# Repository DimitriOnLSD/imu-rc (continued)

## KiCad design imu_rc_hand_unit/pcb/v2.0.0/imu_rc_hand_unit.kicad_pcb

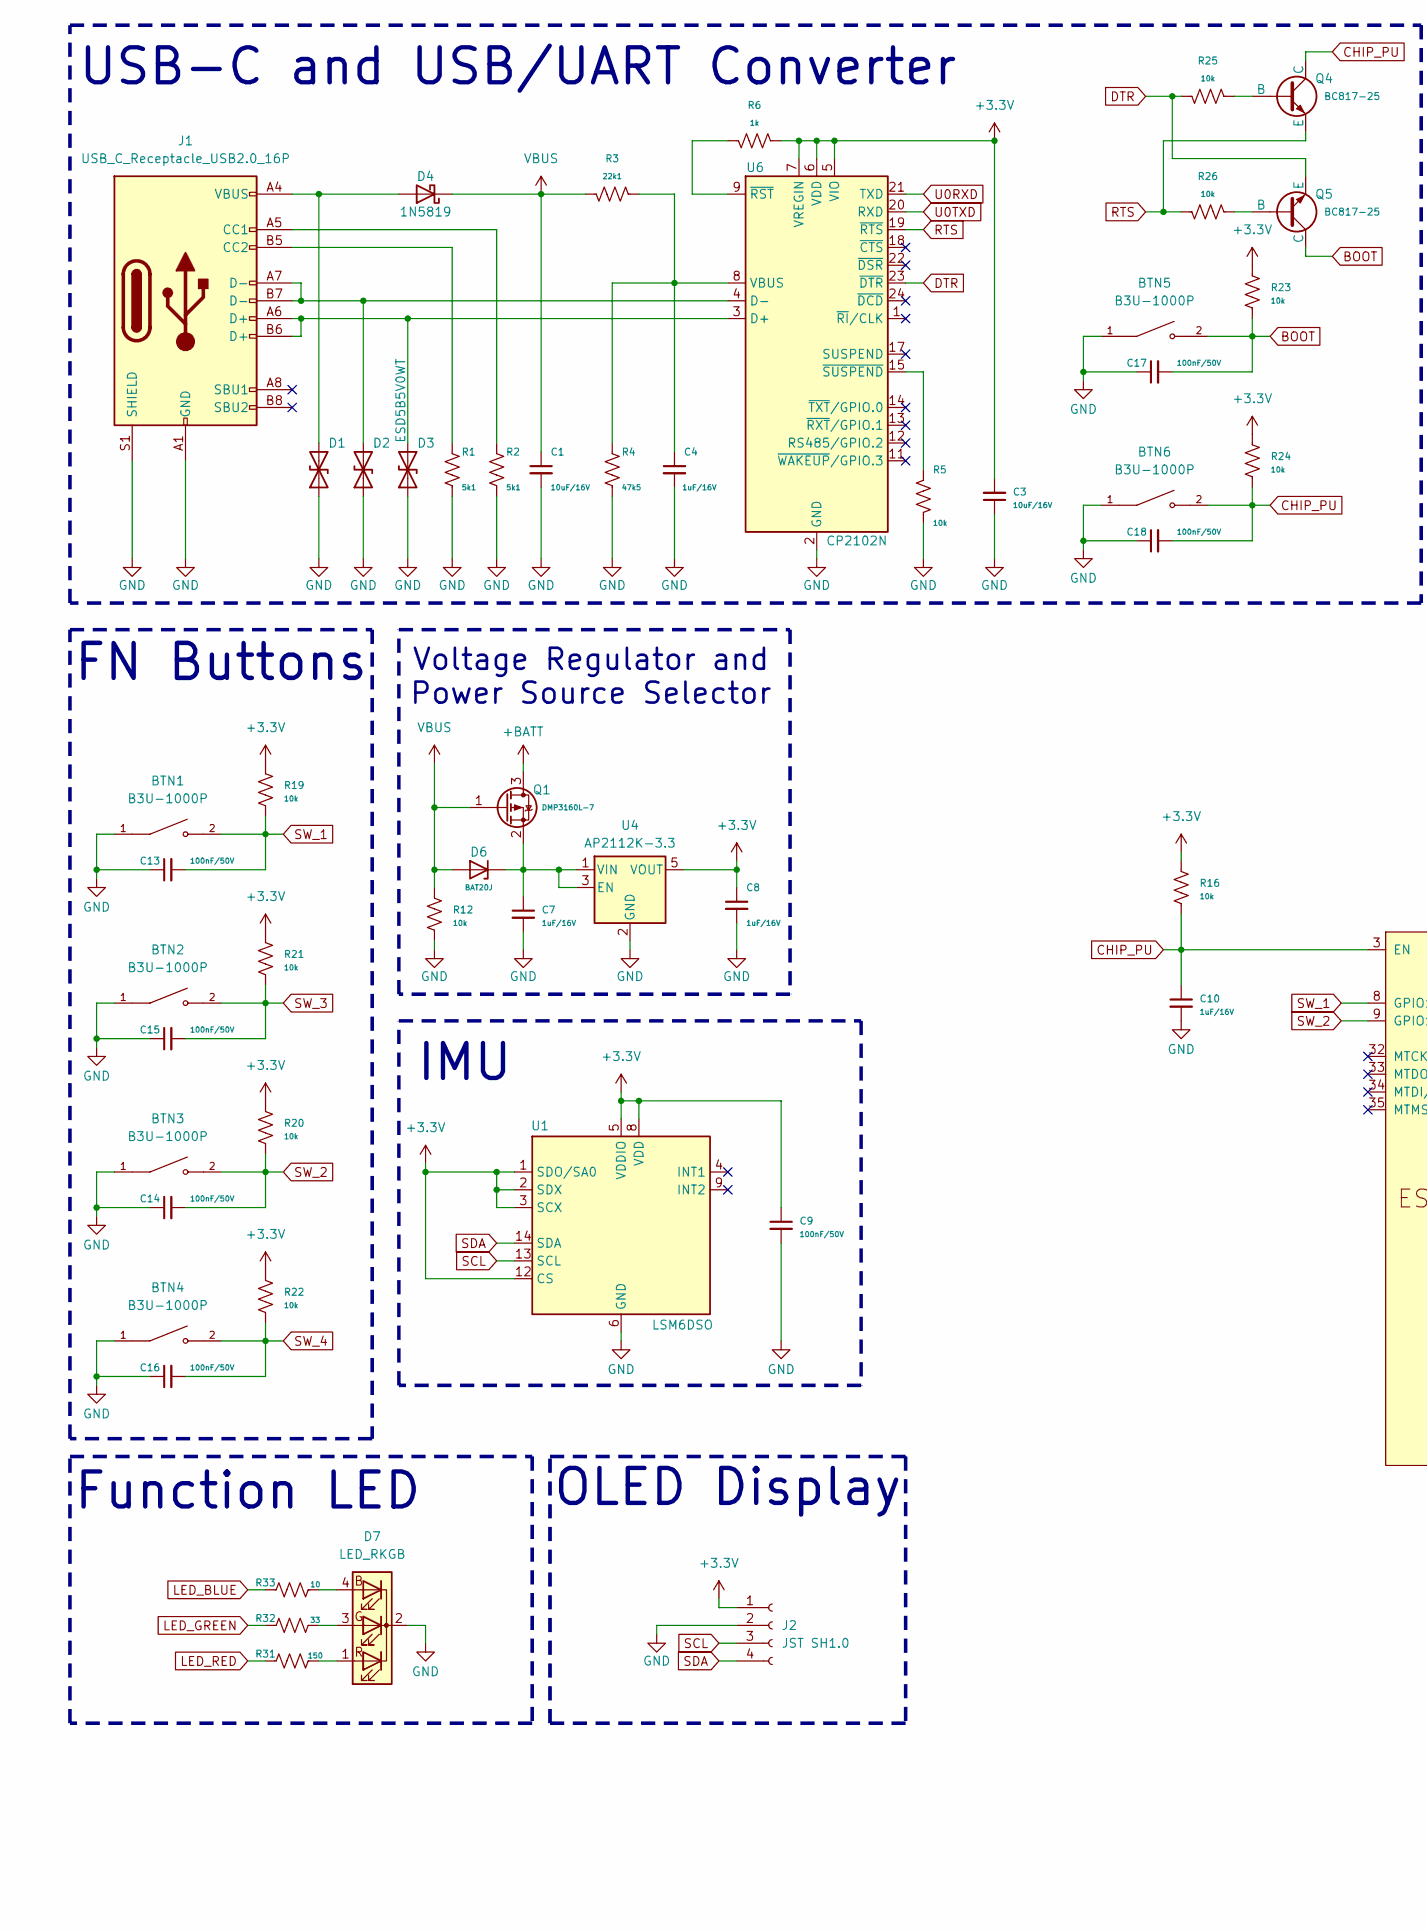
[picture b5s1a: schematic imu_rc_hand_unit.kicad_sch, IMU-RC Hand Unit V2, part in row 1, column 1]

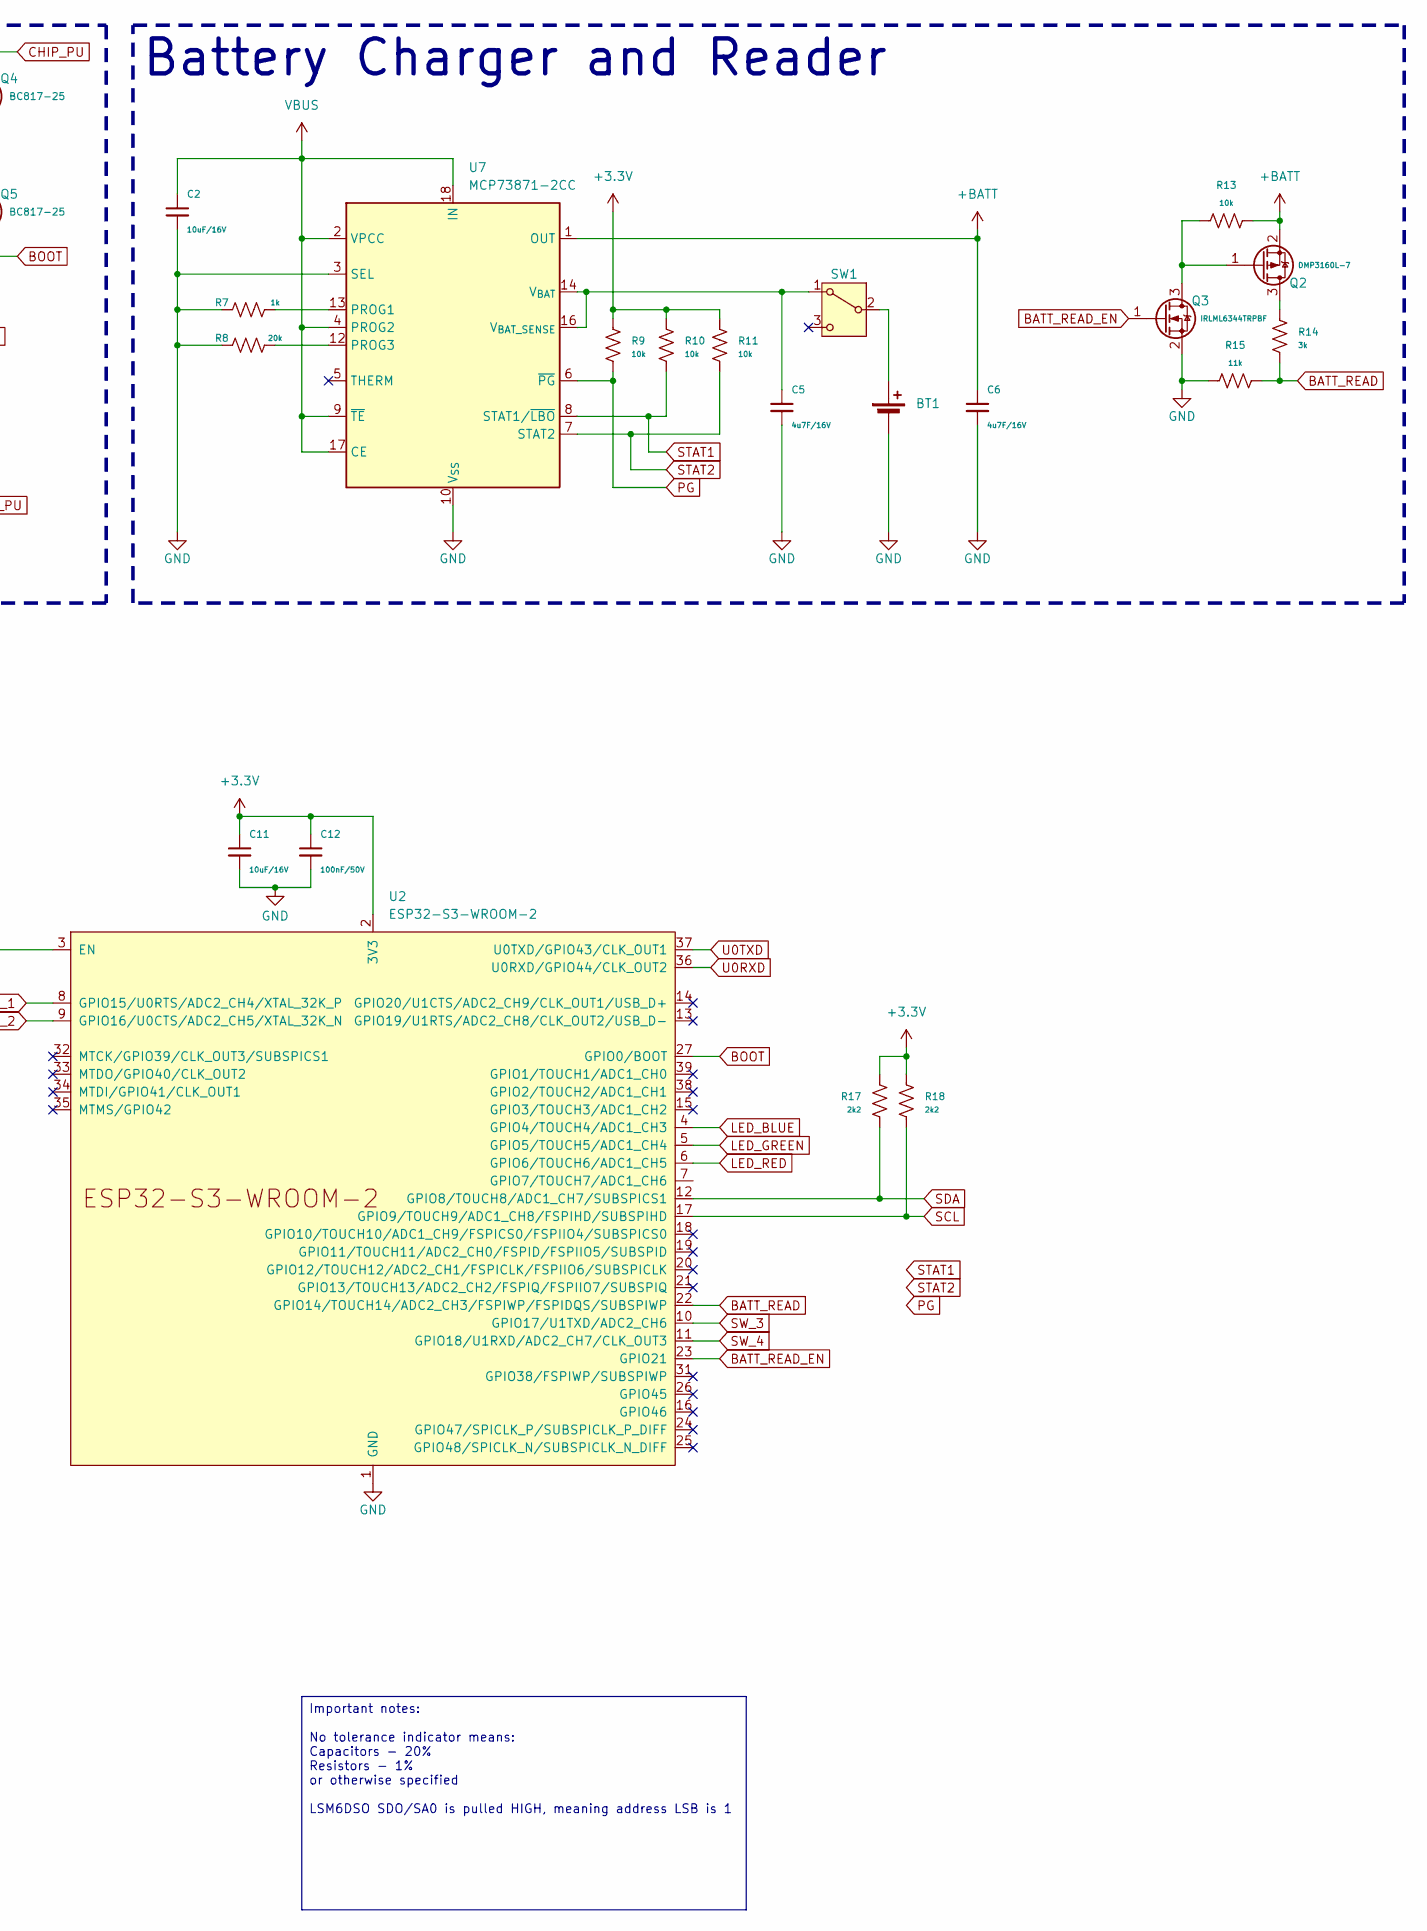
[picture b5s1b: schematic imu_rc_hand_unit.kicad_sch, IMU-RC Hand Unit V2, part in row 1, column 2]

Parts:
BT1: LiPo 3.7V 600mAh; JST_PH_S2B-PH-K_1x02_P2.00mm_Horizontal
BTN1, BTN2, BTN3, BTN4: B3U-1000P; SW_SPST_PTS647_Sx50
BTN5, BTN6: B3U-1000P; SW_SPST_B3U-1000P
C1, C2, C3, C11: 10uF/16V; C_0805_2012Metric
C4, C7, C8, C10: 1uF/16V; C_0805_2012Metric
C5, C6: 4u7F/16V; C_0805_2012Metric
C9, C12, C13, C14, C15, C16, C17, C18: 100nF/50V; C_0805_2012Metric
D1, D2, D3: ESD5B5V0WT; D_SOD-523
D4: 1N5819; D_SOD-123
D6: BAT20J; D_SOD-323
D7: LED_RKGB; LED_D5.0mm-4_RKGB
J1: USB_C_Receptacle_USB2.0_16P; USB_C_Receptacle_GCT_USB4105-xx-A_16P_TopMnt_Horizontal
J2: JST SH1.0; JST_SH_SM04B-SRSS-TB_1x04-1MP_P1.00mm_Horizontal
Q1, Q2: DMP3160L-7; SOT-23
Q3: IRLML6344TRPBF; SOT-23
Q4, Q5: BC817-25; SOT-23
R1, R2: 5k1; R_0805_2012Metric
R3: 22k1; R_0805_2012Metric
R4: 47k5; R_0805_2012Metric
R5, R9, R10, R11, R12, R13, R16, R19, R20, R21, R22, R23, R24, R25, R26: 10k; R_0805_2012Metric
R6, R7: 1k; R_0805_2012Metric
R8: 20k; R_0805_2012Metric
R14: 3k; R_0805_2012Metric
R15: 11k; R_0805_2012Metric
R17, R18: 2k2; R_0805_2012Metric
R31: 150; R_0805_2012Metric
R32: 33; R_0805_2012Metric
R33: 10; R_0805_2012Metric
SW1: SW_SPDT; SW_Slide_SPDT_Angled_CK_OS102011MA1Q
U1: LSM6DSO; LGA-14L_3x2.5mm_P0.5mm
U2: ESP32-S3-WROOM-2
U4: AP2112K-3.3; SOT-23-5
U6: CP2102N; QFN-24-1EP_4x4mm_P0.5mm_EP2.6x2.6mm
U7: MCP73871-2CC; QFN-20-1EP_4x4mm_P0.5mm_EP2.5x2.5mm

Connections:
+3.3V: C3.2, C8.1, C9.1, C11.1, C12.1, J2.1, R6.2, R9.1, R10.1, R11.1, R16.2, R17.1, R18.2, R19.2, R20.2, R21.2, R22.2, R23.2, R24.2, U1.1 (SDO/SA0), U1.2 (SDX), U1.3 (SCX), U1.5 (VDDIO), U1.8 (VDD), U1.12 (CS), U2.2 (3V3), U4.5 (VOUT), U6.5 (VIO), U6.6 (VDD), U6.7 (VREGIN)
+BATT: C6.1, Q1.3 (D), Q2.2 (S), R13.2, U7.1 (OUT), U7.20 (OUT)
BATT_READ: R14.2, R15.1, U2.22 (GPIO14/TOUCH14/ADC2_CH3/FSPIWP/FSPIDQS/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)
BATT_READ_EN: Q3.1 (G), U2.23 (GPIO21)
BOOT: BTN5.2, C17.2, Q5.1 (C), R23.1, U2.27 (GPIO0/BOOT)
CHIP_PU: BTN6.2, C10.1, C18.2, Q4.1 (C), R16.1, R24.1, U2.3 (EN)
DTR: Q5.3 (E), R25.1, U6.23 (~DTR)
GND: BT1.2 (-), BTN1.1, BTN2.1, BTN3.1, BTN4.1, BTN5.1, BTN6.1, C1.2, C2.2, C3.1, C4.2, C5.2, C6.2, C7.2, C8.2, C9.2, C10.2, C11.2, C12.2, C13.1, C14.1, C15.1, C16.1, C17.1, C18.1, D1.1 (A1), D2.1 (A1), D3.1 (A1), D7.2 (K), J1.A1 (GND), J1.A12 (GND), J1.B1 (GND), J1.B12 (GND), J1.S1 (SHIELD), J2.2, Q3.2 (S), R1.1, R2.1, R4.1, R5.2, R7.2, R8.2, R12.1, R15.2, U1.6 (GND), U1.7 (GND), U2.1 (GND), U2.40 (GND), U2.41 (GND), U4.2 (GND), U6.2 (GND), U6.25 (GND), U7.3 (SEL), U7.10 (V_{SS}), U7.11 (V_{SS}), U7.21 (V_{SS})
LED_BLUE: R33.2, U2.4 (GPIO4/TOUCH4/ADC1_CH3)
LED_GREEN: R32.2, U2.5 (GPIO5/TOUCH5/ADC1_CH4)
LED_RED: R31.2, U2.6 (GPIO6/TOUCH6/ADC1_CH5)
unnamed: BT1.1 (+), SW1.2 (B)
unnamed: D1.2 (A2), D4.2 (A), J1.A4 (VBUS), J1.A9 (VBUS), J1.B4 (VBUS), J1.B9 (VBUS)
unnamed: D2.2 (A2), J1.A7 (D-), J1.B7 (D-), U6.4 (D-)
unnamed: D3.2 (A2), J1.A6 (D+), J1.B6 (D+), U6.3 (D+)
unnamed: C7.1, D6.1 (K), Q1.2 (S), U4.1 (VIN), U4.3 (EN)
unnamed: D7.4 (BA), R33.1
unnamed: D7.3 (GA), R32.1
unnamed: D7.1 (RA), R31.1
unnamed: J1.A5 (CC1), R2.2
unnamed: J1.B5 (CC2), R1.2
unnamed: Q2.3 (D), R14.1
unnamed: Q2.1 (G), Q3.3 (D), R13.1
unnamed: Q4.2 (B), R25.2
unnamed: Q5.2 (B), R26.2
unnamed: C5.1, SW1.1 (A), U7.14 (V_{BAT}), U7.15 (V_{BAT}), U7.16 (V_{BAT_SENSE})
unnamed: C4.1, R3.1, R4.2, U6.8 (VBUS)
unnamed: R6.1, U6.9 (~RST)
unnamed: R5.1, U6.15 (~SUSPEND)
unnamed: R7.1, U7.13 (PROG1)
unnamed: R8.1, U7.12 (PROG3)
PG: R9.2, U7.6 (~PG)
RTS: Q4.3 (E), R26.1, U6.19 (~RTS)
SCL: J2.3, R18.1, U1.13 (SCL), U2.17 (GPIO9/TOUCH9/ADC1_CH8/FSPIHD/SUBSPIHD)
SDA: J2.4, R17.2, U1.14 (SDA), U2.12 (GPIO8/TOUCH8/ADC1_CH7/SUBSPICS1)
STAT1: R10.2, U7.8 (STAT1/~LBO)
STAT2: R11.2, U7.7 (STAT2)
SW_1: BTN1.2, C13.2, R19.1, U2.8 (GPIO15/U0RTS/ADC2_CH4/XTAL_32K_P)
SW_2: BTN3.2, C14.2, R20.1, U2.9 (GPIO16/U0CTS/ADC2_CH5/XTAL_32K_N)
SW_3: BTN2.2, C15.2, R21.1, U2.10 (GPIO17/U1TXD/ADC2_CH6)
SW_4: BTN4.2, C16.2, R22.1, U2.11 (GPIO18/U1RXD/ADC2_CH7/CLK_OUT3)
U0RXD: U2.36 (U0RXD/GPIO44/CLK_OUT2), U6.21 (TXD)
U0TXD: U2.37 (U0TXD/GPIO43/CLK_OUT1), U6.20 (RXD)
VBUS: C1.1, C2.1, D4.1 (K), D6.2 (A), Q1.1 (G), R3.2, R12.2, U7.2 (VPCC), U7.4 (PROG2), U7.9 (~TE), U7.17 (CE), U7.18 (IN), U7.19 (IN)

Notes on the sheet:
Voltage Regulator and Power Source Selector
Battery Charger and Reader
FN Buttons
USB-C and USB/UART Converter
IMU
OLED Display
Function LED
Important notes: No tolerance indicator means: Capacitors - 20% Resistors - 1% or otherwise specified LSM6DSO SDO/SA0 is pulled HIGH, meaning address LSB is 1

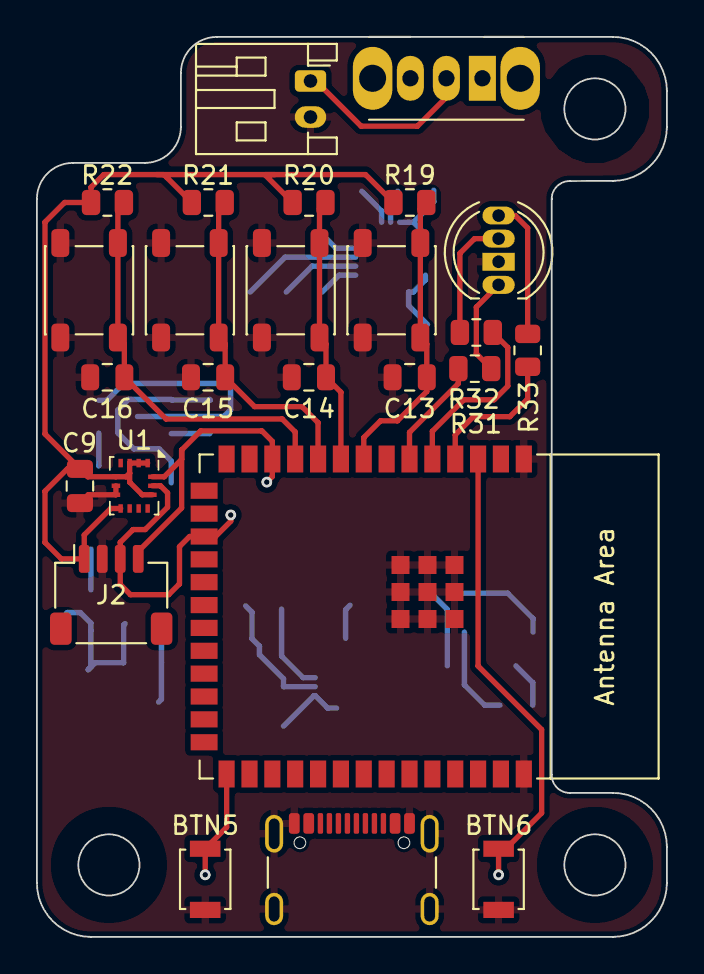
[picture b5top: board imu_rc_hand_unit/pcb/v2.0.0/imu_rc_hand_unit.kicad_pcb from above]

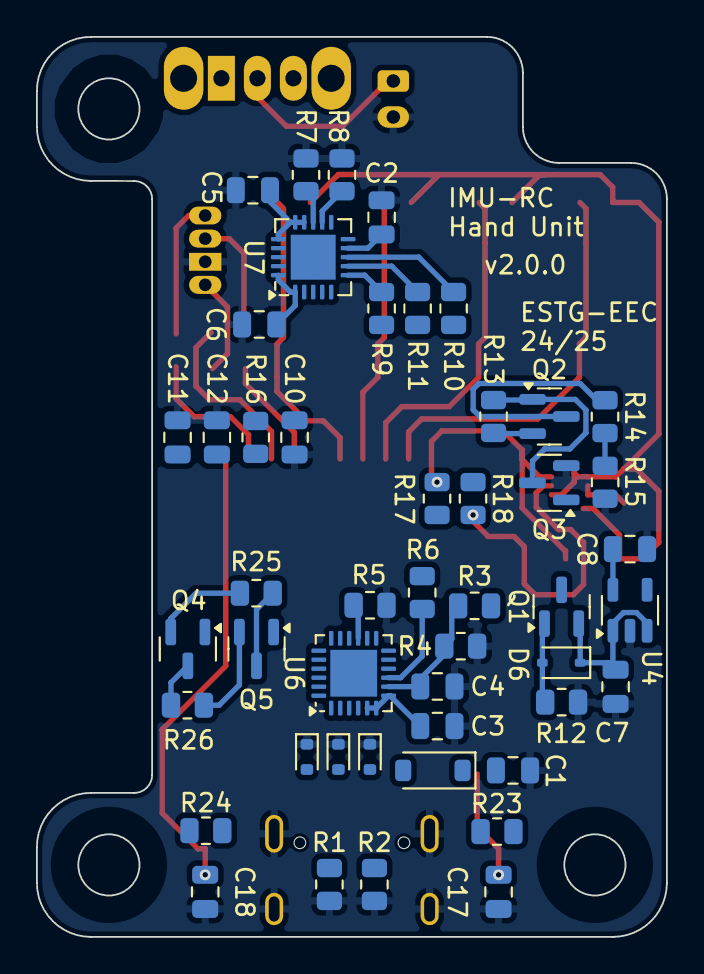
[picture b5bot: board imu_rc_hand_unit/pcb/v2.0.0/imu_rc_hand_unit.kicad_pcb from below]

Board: 2 copper layers, 35.0 x 50.0 mm, 73 parts (48 on the bottom side), 44 nets.

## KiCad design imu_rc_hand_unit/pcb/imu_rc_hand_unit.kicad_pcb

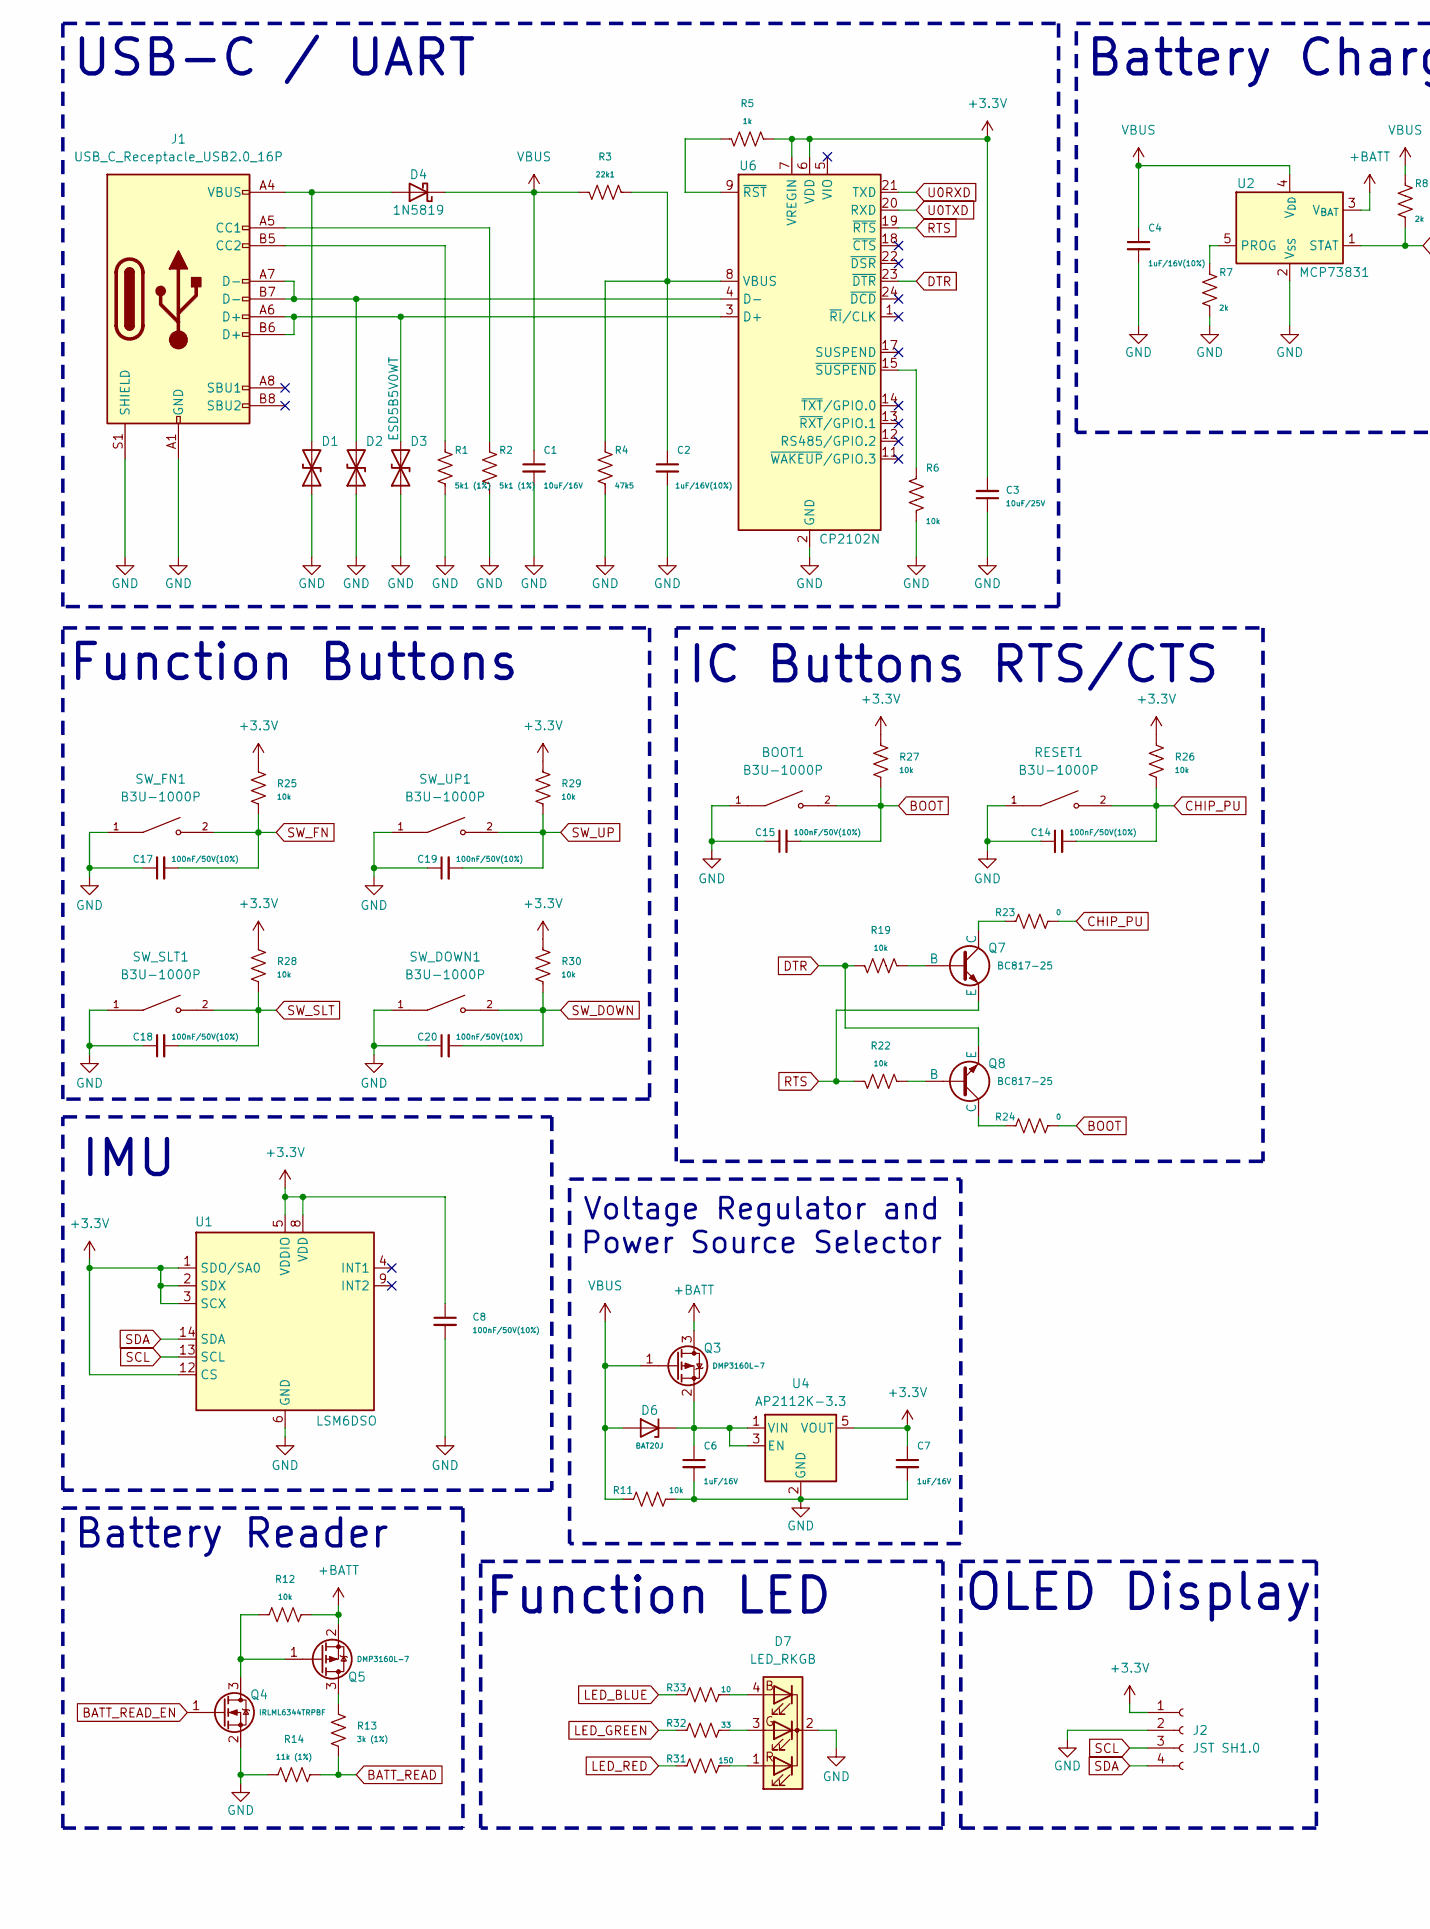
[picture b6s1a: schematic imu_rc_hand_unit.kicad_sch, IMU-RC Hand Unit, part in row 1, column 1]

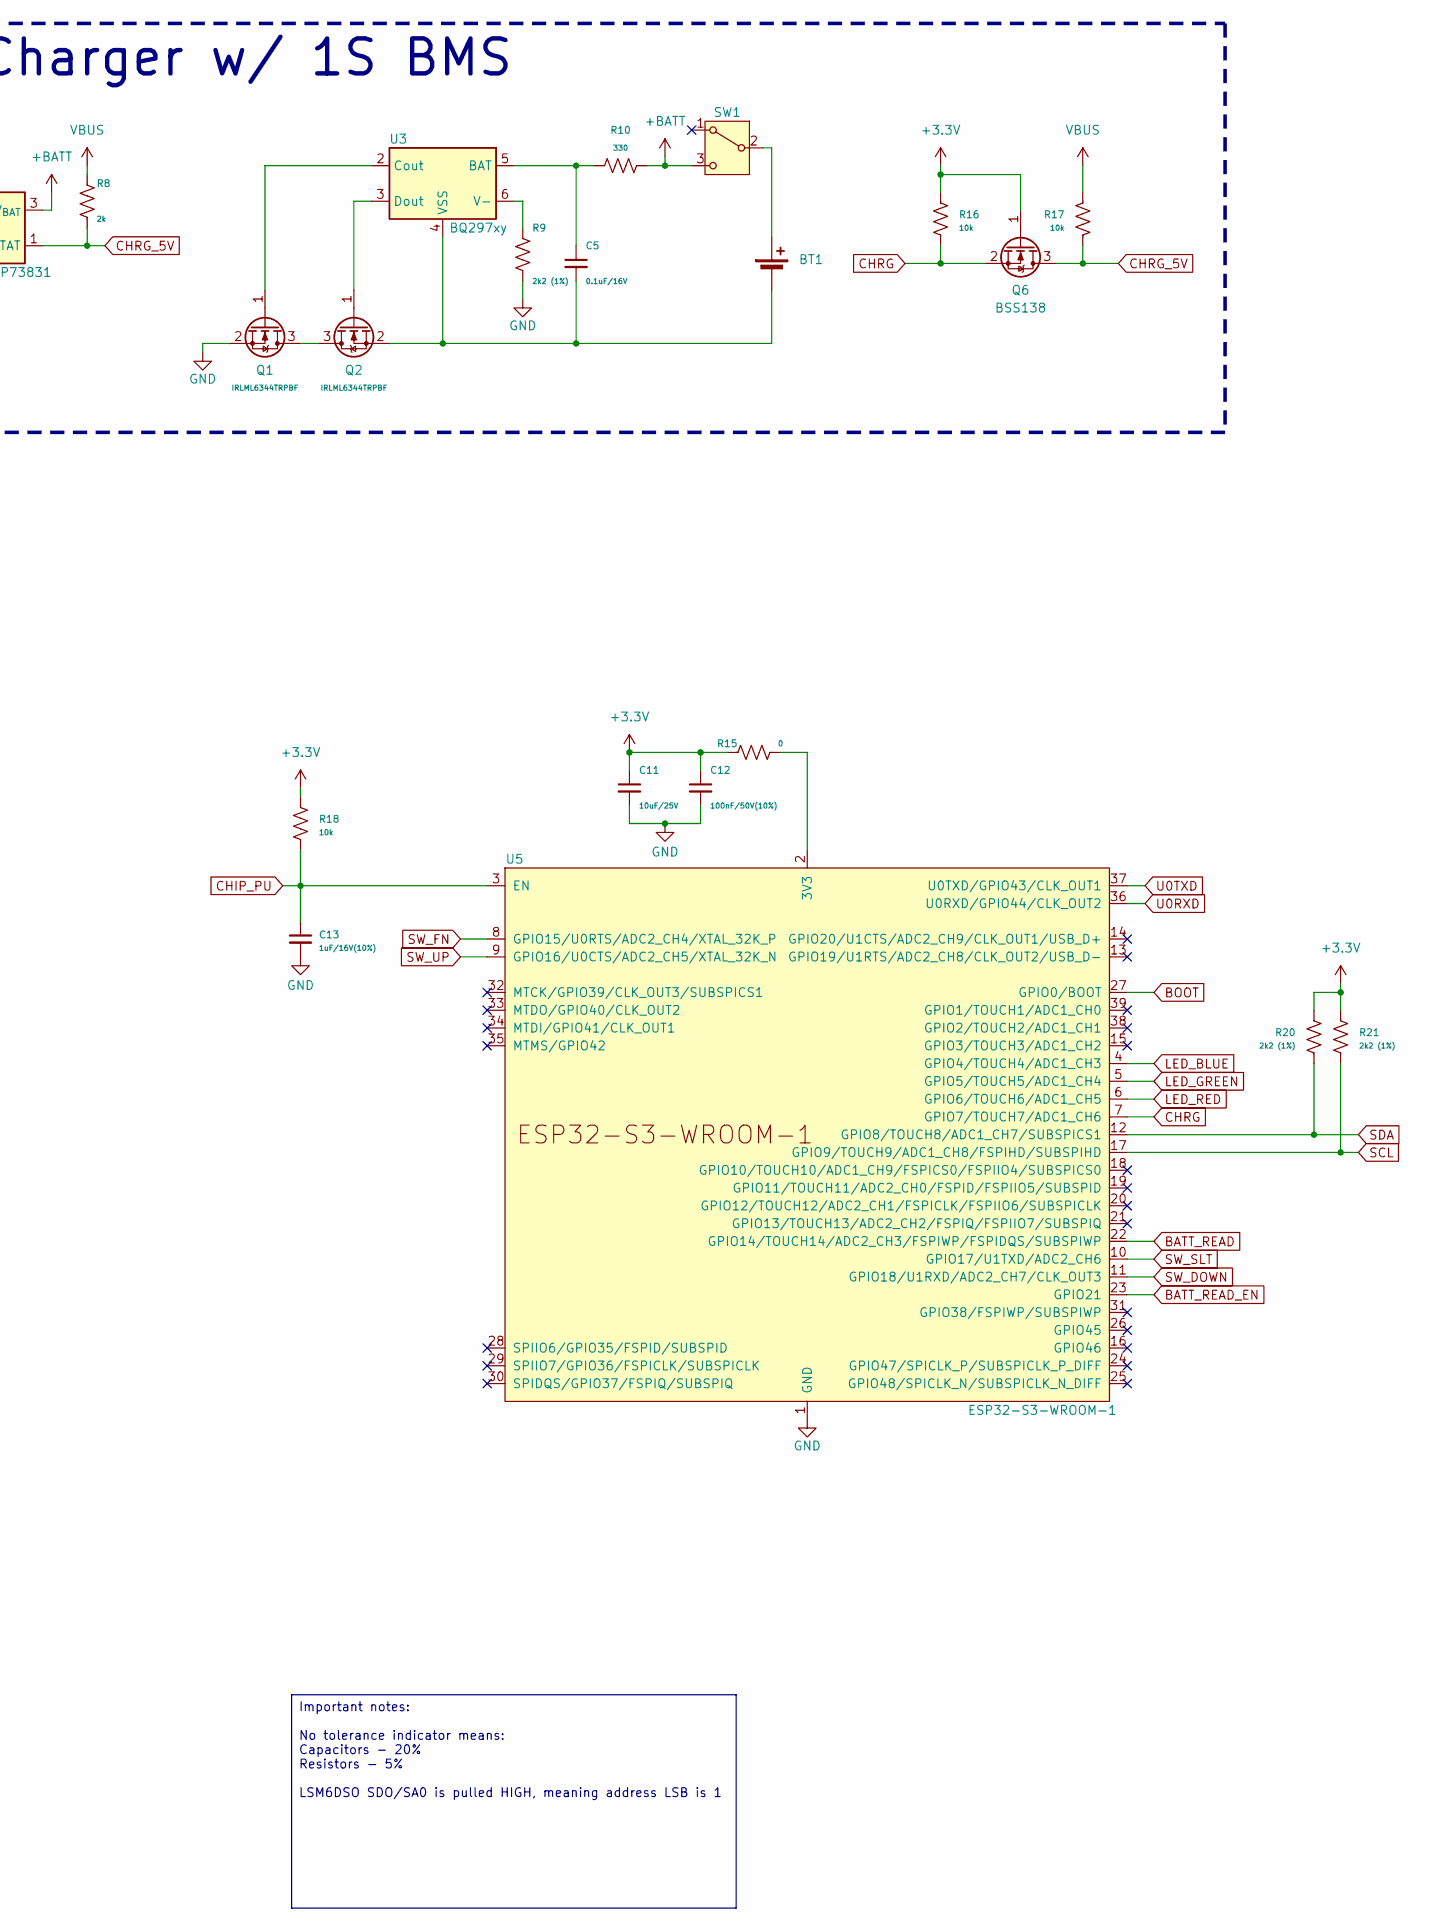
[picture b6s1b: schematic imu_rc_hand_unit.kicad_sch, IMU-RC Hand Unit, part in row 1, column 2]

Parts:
BOOT1: B3U-1000P; SW_SPST_B3U-1000P
BT1: LiPo 3.7V 600mAh; JST_PH_S2B-PH-K_1x02_P2.00mm_Horizontal
C1: 10uF/16V; C_0805_2012Metric
C2, C4: 1uF/16V(10%); C_0603_1608Metric
C3: 10uF/25V; C_0603_1608Metric
C5: 0.1uF/16V; C_0603_1608Metric
C6, C7: 1uF/16V; C_0805_2012Metric
C8, C12, C14, C15, C17, C18, C19, C20: 100nF/50V(10%); C_0805_2012Metric
C11: 10uF/25V; C_0805_2012Metric
C13: 1uF/16V(10%); C_0805_2012Metric
D1, D2: LESD5D5.0CT1G; D_SOD-523
D3: ESD5B5V0WT; D_SOD-523
D4: 1N5819; D_SOD-123
D6: BAT20J; D_SOD-323
D7: LED_RKGB; LED_D5.0mm-4_RKGB
J1: USB_C_Receptacle_USB2.0_16P; USB_C_Receptacle_GCT_USB4105-xx-A_16P_TopMnt_Horizontal
J2: JST SH1.0; JST_SH_SM04B-SRSS-TB_1x04-1MP_P1.00mm_Horizontal
Q1, Q2, Q4: IRLML6344TRPBF; SOT-23
Q3, Q5: DMP3160L-7; SOT-23
Q6: BSS138; SOT-23
Q7, Q8: BC817-25; SOT-23
R1, R2: 5k1 (1%); R_0805_2012Metric
R3: 22k1; R_0805_2012Metric
R4: 47k5; R_0805_2012Metric
R5: 1k; R_0805_2012Metric
R6, R11, R12, R16, R17, R18, R19, R22, R25, R26, R27, R28, R29, R30: 10k; R_0805_2012Metric
R7, R8: 2k; R_0805_2012Metric
R9, R20, R21: 2k2 (1%); R_0805_2012Metric
R10: 330; R_0805_2012Metric
R13: 3k (1%); R_0805_2012Metric
R14: 11k (1%); R_0805_2012Metric
R15, R23, R24: 0; R_1206_3216Metric
R31: 150; R_0805_2012Metric
R32: 33; R_0805_2012Metric
R33: 10; R_0805_2012Metric
RESET1: B3U-1000P; SW_SPST_B3U-1000P
SW1: SW_SPDT; SW_Slide_SPDT_Angled_CK_OS102011MA1Q
SW_DOWN1: B3U-1000P; SW_SPST_PTS647_Sx50
SW_FN1: B3U-1000P; SW_SPST_PTS647_Sx50
SW_SLT1: B3U-1000P; SW_SPST_PTS647_Sx50
SW_UP1: B3U-1000P; SW_SPST_PTS647_Sx50
U1: LSM6DSO; LGA-14L_3x2.5mm_P0.5mm
U2: MCP73831; QFN-20-1EP_4x4mm_P0.5mm_EP2.5x2.5mm
U3: BQ297xy; WSON-6_1.5x1.5mm_P0.5mm
U4: AP2112K-3.3; SOT-23-5
U5: ESP32-S3-WROOM-1
U6: CP2102N; QFN-24-1EP_4x4mm_P0.5mm_EP2.6x2.6mm

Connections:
+3.3V: C3.2, C7.1, C8.1, C11.1, C12.1, J2.1, Q6.1 (G), R5.2, R15.1, R16.2, R18.2, R20.1, R21.2, R25.2, R26.2, R27.2, R28.2, R29.2, R30.2, U1.1 (SDO/SA0), U1.2 (SDX), U1.3 (SCX), U1.5 (VDDIO), U1.8 (VDD), U1.12 (CS), U4.5 (VOUT), U6.6 (VDD), U6.7 (VREGIN)
+BATT: Q3.3 (D), Q5.2 (S), R10.2, R12.2, SW1.3 (C), U2.3 (V_{BAT})
BATT_READ: R13.2, R14.1, U5.22 (GPIO14/TOUCH14/ADC2_CH3/FSPIWP/FSPIDQS/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)
BATT_READ_EN: Q4.1 (G), U5.23 (GPIO21)
BOOT: BOOT1.2, C15.2, R24.2, R27.1, U5.27 (GPIO0/BOOT)
CHIP_PU: C13.1, C14.2, R18.1, R23.2, R26.1, RESET1.2, U5.3 (EN)
CHRG: Q6.2 (S), R16.1, U5.7 (GPIO7/TOUCH7/ADC1_CH6)
CHRG_5V: Q6.3 (D), R8.2, R17.1, U2.1 (STAT)
DTR: Q8.3 (E), R19.1, U6.23 (~DTR)
GND: BOOT1.1, C1.2, C2.2, C3.1, C4.2, C6.2, C7.2, C8.2, C11.2, C12.2, C13.2, C14.1, C15.1, C17.1, C18.1, C19.1, C20.1, D1.1 (A1), D2.1 (A1), D3.1 (A1), D7.2 (K), J1.A1 (GND), J1.A12 (GND), J1.B1 (GND), J1.B12 (GND), J1.S1 (SHIELD), J2.2, Q1.2 (S), Q4.2 (S), R1.1, R2.1, R4.1, R6.2, R7.2, R9.1, R11.1, R14.2, RESET1.1, SW_DOWN1.1, SW_FN1.1, SW_SLT1.1, SW_UP1.1, U1.6 (GND), U1.7 (GND), U2.2 (V_{SS}), U4.2 (GND), U5.1 (GND), U5.40 (GND), U5.41 (GND), U6.2 (GND), U6.25 (GND)
LED_BLUE: R33.2, U5.4 (GPIO4/TOUCH4/ADC1_CH3)
LED_GREEN: R32.2, U5.5 (GPIO5/TOUCH5/ADC1_CH4)
LED_RED: R31.2, U5.6 (GPIO6/TOUCH6/ADC1_CH5)
unnamed: BT1.1 (+), SW1.2 (B)
unnamed: BT1.2 (-), C5.2, Q2.2 (S), U3.4 (VSS)
unnamed: D1.2 (A2), D4.2 (A), J1.A4 (VBUS), J1.A9 (VBUS), J1.B4 (VBUS), J1.B9 (VBUS)
unnamed: D2.2 (A2), J1.A7 (D-), J1.B7 (D-), U6.4 (D-)
unnamed: D3.2 (A2), J1.A6 (D+), J1.B6 (D+), U6.3 (D+)
unnamed: C6.1, D6.1 (K), Q3.2 (S), U4.1 (VIN), U4.3 (EN)
unnamed: D7.4 (BA), R33.1
unnamed: D7.3 (GA), R32.1
unnamed: D7.1 (RA), R31.1
unnamed: J1.A5 (CC1), R2.2
unnamed: J1.B5 (CC2), R1.2
unnamed: Q1.3 (D), Q2.3 (D)
unnamed: Q1.1 (G), U3.2 (Cout)
unnamed: Q2.1 (G), U3.3 (Dout)
unnamed: Q4.3 (D), Q5.1 (G), R12.1
unnamed: Q5.3 (D), R13.1
unnamed: Q7.2 (B), R19.2
unnamed: Q7.1 (C), R23.1
unnamed: Q8.2 (B), R22.2
unnamed: Q8.1 (C), R24.1
unnamed: R7.1, U2.5 (PROG)
unnamed: C5.1, R10.1, U3.5 (BAT)
unnamed: R9.2, U3.6 (V-)
unnamed: R15.2, U5.2 (3V3)
unnamed: C2.1, R3.1, R4.2, U6.8 (VBUS)
unnamed: R5.1, U6.9 (~RST)
unnamed: R6.1, U6.15 (~SUSPEND)
RTS: Q7.3 (E), R22.1, U6.19 (~RTS)
SCL: J2.3, R21.1, U1.13 (SCL), U5.17 (GPIO9/TOUCH9/ADC1_CH8/FSPIHD/SUBSPIHD)
SDA: J2.4, R20.2, U1.14 (SDA), U5.12 (GPIO8/TOUCH8/ADC1_CH7/SUBSPICS1)
SW_DOWN: C20.2, R30.1, SW_DOWN1.2, U5.11 (GPIO18/U1RXD/ADC2_CH7/CLK_OUT3)
SW_FN: C17.2, R25.1, SW_FN1.2, U5.8 (GPIO15/U0RTS/ADC2_CH4/XTAL_32K_P)
SW_SLT: C18.2, R28.1, SW_SLT1.2, U5.10 (GPIO17/U1TXD/ADC2_CH6)
SW_UP: C19.2, R29.1, SW_UP1.2, U5.9 (GPIO16/U0CTS/ADC2_CH5/XTAL_32K_N)
U0RXD: U5.36 (U0RXD/GPIO44/CLK_OUT2), U6.21 (TXD)
U0TXD: U5.37 (U0TXD/GPIO43/CLK_OUT1), U6.20 (RXD)
VBUS: C1.1, C4.1, D4.1 (K), D6.2 (A), Q3.1 (G), R3.2, R8.1, R11.2, R17.2, U2.4 (V_{DD})

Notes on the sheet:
Voltage Regulator and Power Source Selector
Battery Charger w/ 1S BMS
Function Buttons
IC Buttons RTS/CTS
USB-C / UART
Battery Reader
IMU
OLED Display
Function LED
Important notes: No tolerance indicator means: Capacitors - 20% Resistors - 5% LSM6DSO SDO/SA0 is pulled HIGH, meaning address LSB is 1

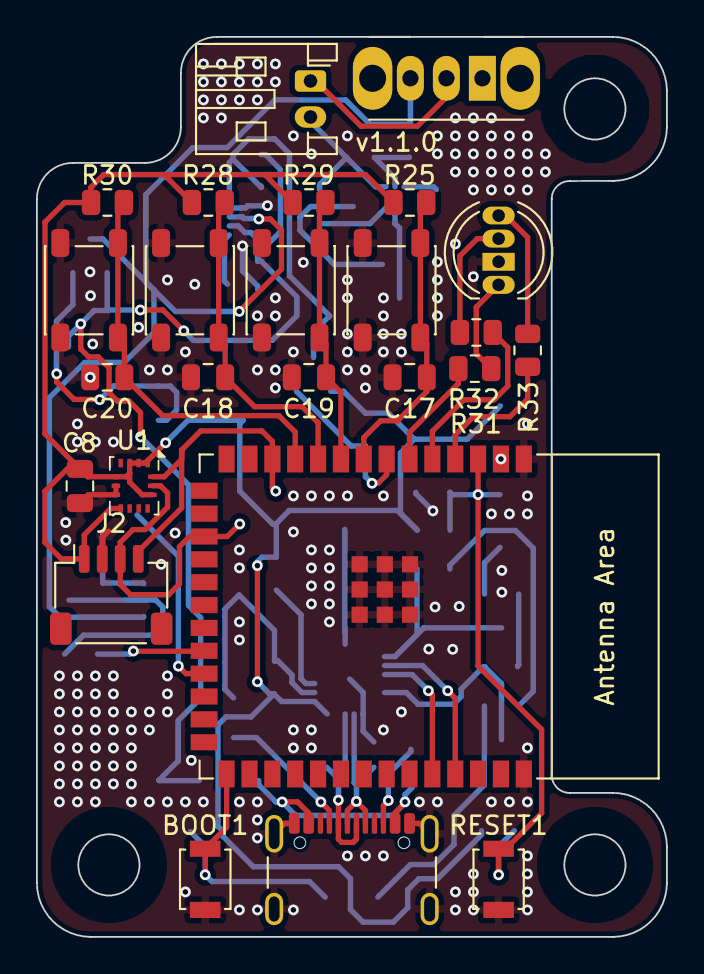
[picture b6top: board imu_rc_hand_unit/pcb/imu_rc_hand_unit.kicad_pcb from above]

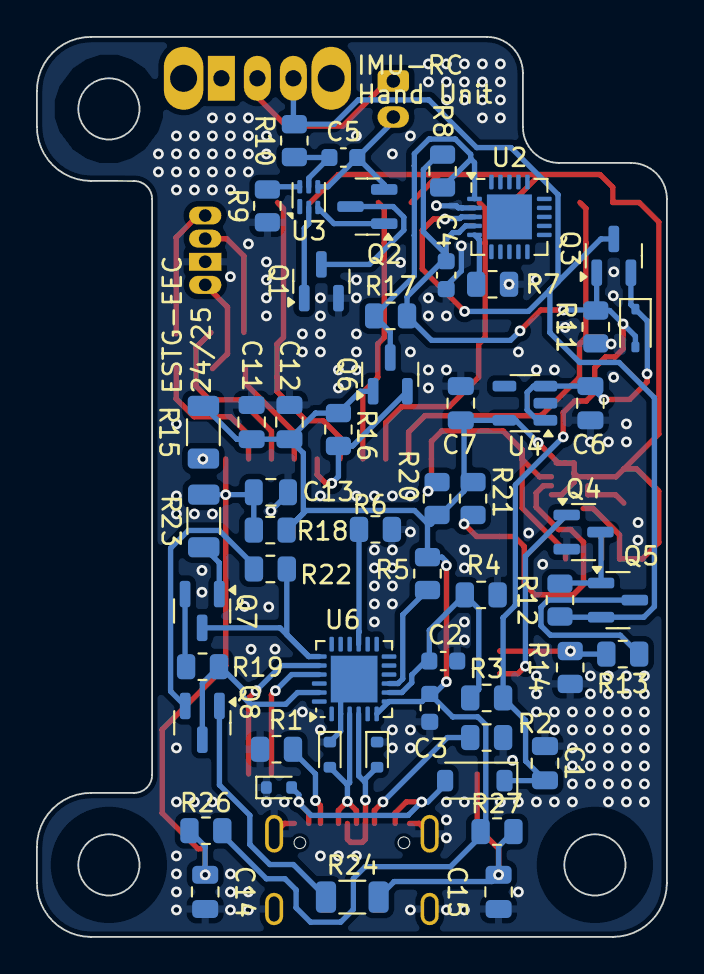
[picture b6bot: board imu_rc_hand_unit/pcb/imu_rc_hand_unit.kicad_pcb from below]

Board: 2 copper layers, 35.0 x 50.0 mm, 80 parts (55 on the bottom side), 50 nets.

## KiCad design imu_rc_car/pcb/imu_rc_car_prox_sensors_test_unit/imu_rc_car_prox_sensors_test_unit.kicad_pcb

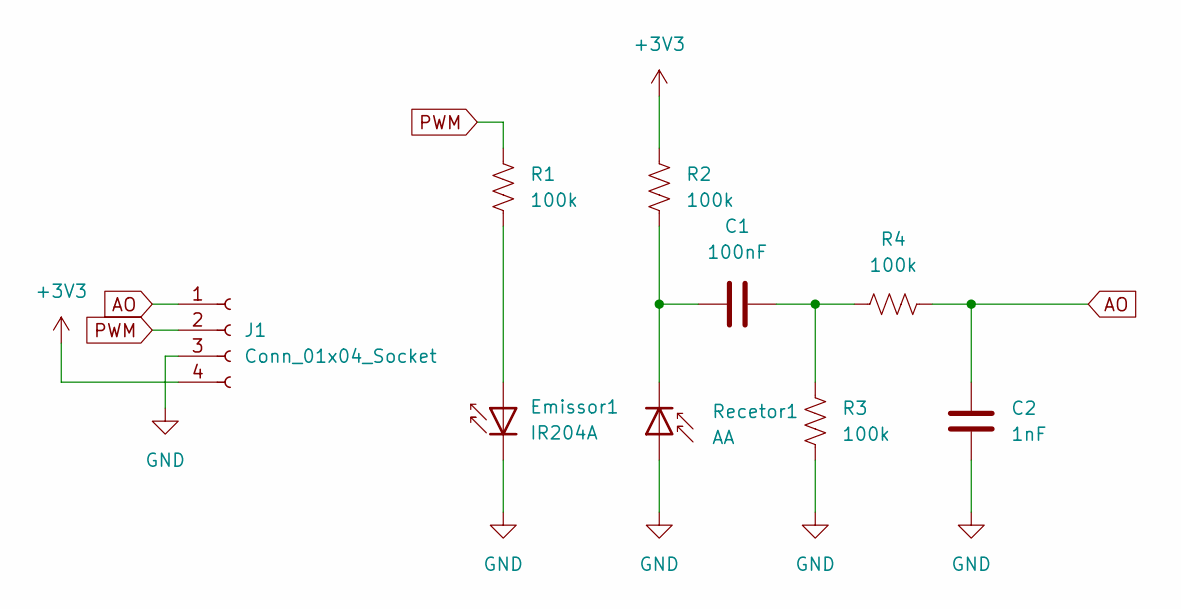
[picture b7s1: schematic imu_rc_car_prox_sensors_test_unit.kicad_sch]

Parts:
C1: 100nF; C_Disc_D5.0mm_W2.5mm_P5.00mm
C2: 1nF; C_Disc_D5.0mm_W2.5mm_P5.00mm
Emissor1: IR204A; LED_D5.0mm_Horizontal_O1.27mm_Z3.0mm_Clear
J1: Conn_01x04_Socket; PinHeader_1x04_P2.54mm_Horizontal
R1, R2, R3, R4: 100k; R_Axial_DIN0204_L3.6mm_D1.6mm_P5.08mm_Horizontal
Recetor1: AA; LED_D5.0mm_Horizontal_O1.27mm_Z3.0mm_IRBlack

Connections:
+3V3: J1.4, R2.2
AO: C2.2, J1.1, R4.1
GND: C2.1, Emissor1.1 (K), J1.3, R3.1, Recetor1.2 (A)
unnamed: C1.2, R3.2, R4.2
unnamed: Emissor1.2 (A), R1.1
unnamed: C1.1, R2.1, Recetor1.1 (K)
PWM: J1.2, R1.2

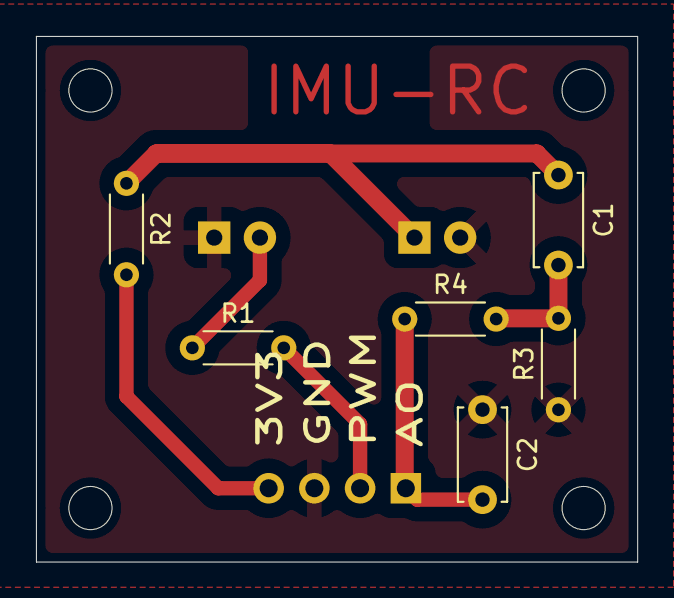
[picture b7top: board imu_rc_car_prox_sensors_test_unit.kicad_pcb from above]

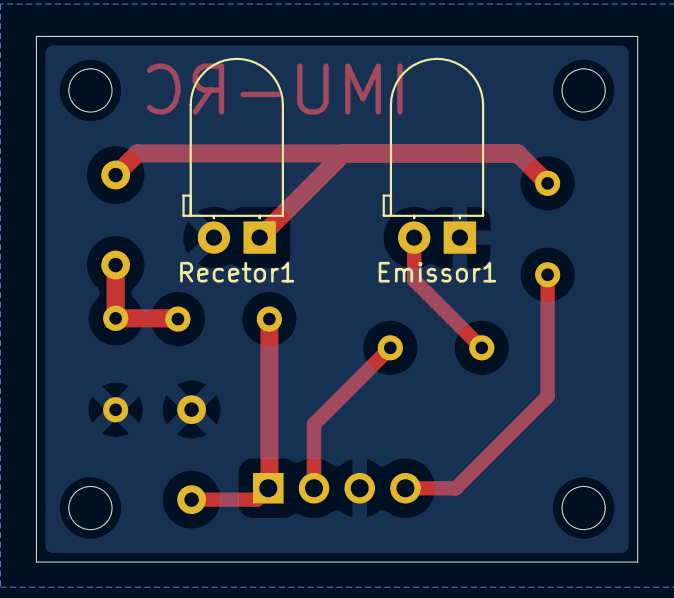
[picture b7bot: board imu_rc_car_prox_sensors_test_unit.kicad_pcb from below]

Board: 2 copper layers, 33.4 x 29.2 mm, 9 parts (2 on the bottom side), 7 nets.

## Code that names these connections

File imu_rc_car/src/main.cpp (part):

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#define CHARACTERISTIC_UUID "3e2c8a88-90fd-4b6b-b947-997e80d03d5b"

// Define motor control pins for DRV8833 driver
#define AIN1 35  // RIGHT LEFT motor - input 1
#define AIN2 45  // RIGHT LEFT motor - input 2
#define BIN1 48  // FRONT LEFT motor - input 1 ALTERADO COM BIN2
#define BIN2 47  // FRONT LEFT motor - input 2 ALTERADO COM BIN1
#define AIN3 15  // FRONT RIGHT motor - input 1 ALTERADO COM AIN4
#define AIN4 16  // FRONT RIGHT motor - input 2 ALTERADO COM AIN3
#define BIN3 6   // REAR RIGHT motor - input 1
#define BIN4 7   // REAR RIGHT motor - input 2

// Define standby pins for DRV8833 driver
#define STNDBYA 36
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
// Function to configure motor pins and attach PWM channels
void setupMotorPins() {
  pinMode(AIN1, OUTPUT); pinMode(AIN2, OUTPUT);
  pinMode(BIN1, OUTPUT); pinMode(BIN2, OUTPUT);
  pinMode(AIN3, OUTPUT); pinMode(AIN4, OUTPUT);
  pinMode(BIN3, OUTPUT); pinMode(BIN4, OUTPUT);

  pinMode(STNDBYA, OUTPUT);
  pinMode(STNDBYB, OUTPUT);

  ledcSetup(AIN1_CH, FREQUENCY, RESOLUTION); ledcAttachPin(AIN1, AIN1_CH);
  ledcSetup(AIN2_CH, FREQUENCY, RESOLUTION); ledcAttachPin(AIN2, AIN2_CH);
  ledcSetup(BIN1_CH, FREQUENCY, RESOLUTION); ledcAttachPin(BIN1, BIN1_CH);
  ledcSetup(BIN2_CH, FREQUENCY, RESOLUTION); ledcAttachPin(BIN2, BIN2_CH);
  ledcSetup(AIN3_CH, FREQUENCY, RESOLUTION); ledcAttachPin(AIN3, AIN3_CH);
  ledcSetup(AIN4_CH, FREQUENCY, RESOLUTION); ledcAttachPin(AIN4, AIN4_CH);
  ledcSetup(BIN3_CH, FREQUENCY, RESOLUTION); ledcAttachPin(BIN3, BIN3_CH);
  ledcSetup(BIN4_CH, FREQUENCY, RESOLUTION); ledcAttachPin(BIN4, BIN4_CH);

  move(0); // Stop all motors initially
}
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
